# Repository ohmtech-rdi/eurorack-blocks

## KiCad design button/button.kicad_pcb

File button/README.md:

# button

## Description

This block is a simple trigger push button.
Its design is detailed [here](./documentation/design.md).

## Connecting

- This block needs its `GND` to be connected to the ground. All `GND` pins are connected
   internally.
- The signal `OUT` is the button signal. It should be connected to any GPIO of the
   target MCU, **preferably non-analog** GPIOs. See [Daisy Seed pinout](https://images.squarespace-cdn.com/content/v1/58d03fdc1b10e3bf442567b8/1591827747342-HCXMM2NNR26SP5F4U2CJ/ke17ZwdGBToddI8pDm48kN5PbQBGNYbW-5Hm1pf8hRF7gQa3H78H3Y0txjaiv_0fDoOvxcdMmMKkDsyUqMSsMWxHk725yiiHCCLfrh8O1z4YTzHvnKhyp6Da-NYroOW3ZGjoBKy3azqku80C789l0kLp48N9LluBiCpBrPZntaz462IffsVrAff3VJkwKncM1HZuDnV98dfxM9yHlqFkUQ/DaisyPinoutRev4%404x.png?format=500w) for details.

## Using

```c++
int main ()
{
   using namespace erb;
   
   Module module;
   Button button (module, Pin23);   // 1.
   
   module.run ([&](){
      if (button.pressed ()) ...    // 2.
      if (button.held ()) ...       // 3.
      if (button.released ()) ...   // 4.
   });
}
```

1. Attach the button to the module and specify the same pin as the one used for connecting,
2. The button was just pressed,
3. The button is held down,
4. The button was just released.

The `Button` class reference is available [here](./documentation/reference.md).

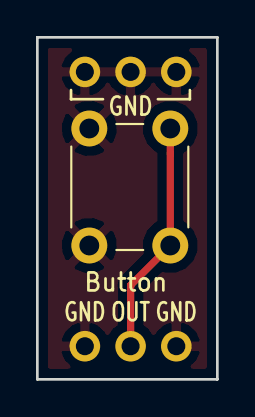
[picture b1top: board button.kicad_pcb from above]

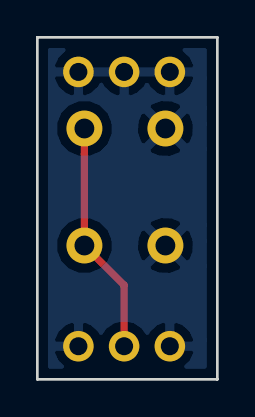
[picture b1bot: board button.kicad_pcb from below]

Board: 2 copper layers, 10.0 x 19.0 mm, 3 parts (2 on the bottom side), 2 nets.

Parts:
J1: POWER; PinHeader_1x03_P2.54mm_Vertical
J2: OUT; PinHeader_1x03_P2.54mm_Vertical
SW1: SW_Push_Dual; SW_PUSH_6mm_H7.3mm

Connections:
GND: J1.1, J1.2, J1.3, J2.1, J2.3, SW1.1
OUT: J2.2, SW1.2

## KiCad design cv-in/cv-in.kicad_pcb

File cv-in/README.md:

# cv-in

## Description

This block is a simple analog CV input.
Its design is detailed [here](./documentation/design.md).

## Connecting

- This block needs its `GND` to be connected to the ground. All `GND` pins are connected
   internally,
- This block needs its `-12V` to be connected to the `-12V` of the `power-bus`,
- This block needs its `3V3A` to be connected to the Daisy Seed 3V3 Analog Power I/O on Pin 21,
- The `NOP` pin can be either connected to:
   - `GND` to send (slightly noisy) zeros to the software implementation,
   - Cascading the `DI` signal from another `cv-in` block,
   - A pseudo-random predefined signal to detect a jack connection
      as explained on the Mutable Instruments forums
      [here](https://forum.mutable-instruments.net/t/plaits-normalization-probe/14358/2)
      and implemented
      [here](https://github.com/pichenettes/eurorack/blob/master/plaits/ui.cc#L368).
- The signal `OUT` is the CV input signal. It should be connected to any Analog GPIO of the
   target MCU. See [Daisy Seed pinout](https://images.squarespace-cdn.com/content/v1/58d03fdc1b10e3bf442567b8/1591827747342-HCXMM2NNR26SP5F4U2CJ/ke17ZwdGBToddI8pDm48kN5PbQBGNYbW-5Hm1pf8hRF7gQa3H78H3Y0txjaiv_0fDoOvxcdMmMKkDsyUqMSsMWxHk725yiiHCCLfrh8O1z4YTzHvnKhyp6Da-NYroOW3ZGjoBKy3azqku80C789l0kLp48N9LluBiCpBrPZntaz462IffsVrAff3VJkwKncM1HZuDnV98dfxM9yHlqFkUQ/DaisyPinoutRev4%404x.png?format=500w) for details.

The `DI` pin is the signal coming out directly from the jack connector and should be left floating
if not used.

The pseudo-random predefined signal jack detection method allows,
from a user experience point of view, to dissociate a non-connected
jack from a connected jack at `GND` level.

## Using

```c++
int main ()
{
   using namespace erb;
   
   Module module;
   CvIn cv_in (module, AdcPin6);    // 1.
   
   module.run ([&](){
      float cv_value = cv_in;       // 2.
   });
}
```

1. Attach the CV to the module and specify the same analog pin as the one used for connecting,
2. Retrieve the bipolar (in the `-1.f` to `1.f` range) floating-point CV value from the
   -8V to 8V electrical range.

The `CvIn` class reference is available [here](./documentation/reference.md).

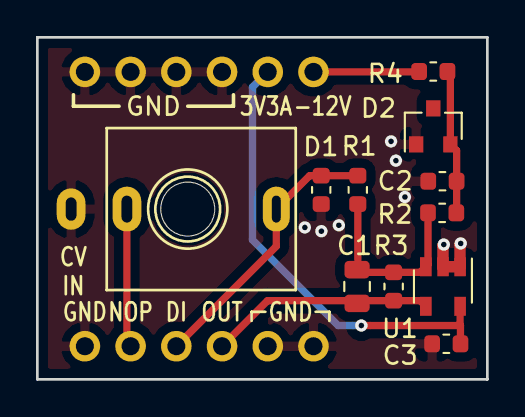
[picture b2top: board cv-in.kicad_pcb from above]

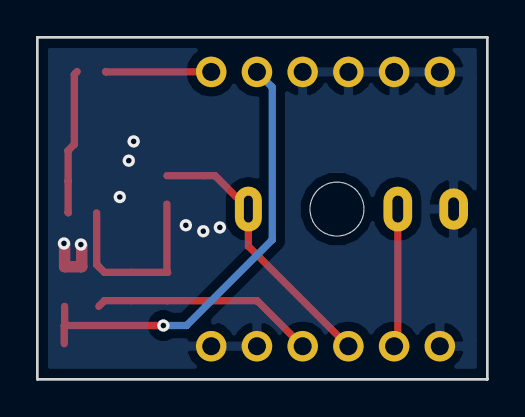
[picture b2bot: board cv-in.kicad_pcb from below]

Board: 2 copper layers, 25.0 x 19.0 mm, 13 parts (2 on the bottom side), 8 nets.

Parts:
C1: 33n; C_0805_2012Metric
C2: 1u; C_0603_1608Metric
C3: 100n; C_0603_1608Metric
D1: D_TVS; R_0603_1608Metric
D2: LM4040DBZ-10; SOT-23
J1: IN; ThonkiconnJack
J2: OUT; PinHeader_1x06_P2.54mm_Vertical
J3: POWER; PinHeader_1x06_P2.54mm_Vertical
R1: 100k; R_0603_1608Metric
R2: 120k; R_0603_1608Metric
R3: 20k; R_0603_1608Metric
R4: 4.99k; R_0603_1608Metric
U1: MCP6001U; SOT-23-5

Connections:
+3V3: C3.2, J3.5, U1.5
-12V: J3.6, R4.2
DI: D1.1, J1.T, J2.4, R1.2
GND: C2.1, C3.1, D1.2, D2.1, J1.S, J2.1, J2.2, J2.6, J3.1, J3.2, J3.3, J3.4, U1.1, U1.2
NOP: J1.TN, J2.5
unnamed: C1.2, R1.1, R2.1, R3.2, U1.3
OUT: C1.1, J2.3, R3.1, U1.4
VREF-10: C2.2, D2.2, R2.2, R4.1

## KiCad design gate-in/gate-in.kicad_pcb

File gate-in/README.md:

# gate-in

## Description

This block is a simple gate input.
Its design is detailed [here](./documentation/design.md).

## Connecting

- This block needs its `GND` to be connected to the ground. All `GND` pins are connected
   internally,
- This block needs its `3V3D` to be connected to the Daisy Seed 3V3 Digital Power I/O on Pin 38,
- The `NOP` pin can be either connected to:
   - `GND` to send zeros to the software implementation,
   - Cascading the `DI` signal from another `gate-in` block,
   - A pseudo-random predefined signal to detect a jack connection
      as explained on the Mutable Instruments forums
      [here](https://forum.mutable-instruments.net/t/plaits-normalization-probe/14358/2)
      and implemented
      [here](https://github.com/pichenettes/eurorack/blob/master/plaits/ui.cc#L368).
- The signal `OUT` is the Gate input signal. It should be connected to any Digital
   (and preferably non-Analog) GPIO
   of the target MCU. See [Daisy Seed pinout](https://images.squarespace-cdn.com/content/v1/58d03fdc1b10e3bf442567b8/1591827747342-HCXMM2NNR26SP5F4U2CJ/ke17ZwdGBToddI8pDm48kN5PbQBGNYbW-5Hm1pf8hRF7gQa3H78H3Y0txjaiv_0fDoOvxcdMmMKkDsyUqMSsMWxHk725yiiHCCLfrh8O1z4YTzHvnKhyp6Da-NYroOW3ZGjoBKy3azqku80C789l0kLp48N9LluBiCpBrPZntaz462IffsVrAff3VJkwKncM1HZuDnV98dfxM9yHlqFkUQ/DaisyPinoutRev4%404x.png?format=500w) for details.

The `DI` pin is the signal coming out directly from the jack connector and should be left floating
if not used.

The pseudo-random predefined signal jack detection method allows,
from a user experience point of view, to dissociate a non-connected
jack from a connected jack at `GND` level.

## Using

```c++
int main ()
{
   using namespace erb;
   
   Module module;
   GateIn gate_in (module, Pin7);   // 1.
   
   module.run ([&](){
      bool gate_value = gate_in;    // 2.
   });
}
```

1. Attach the gate to the module and specify the same digital pin as the one used for connecting,
2. Retrieve the boolean gate value.

The `GateIn` class reference is available [here](./documentation/reference.md).

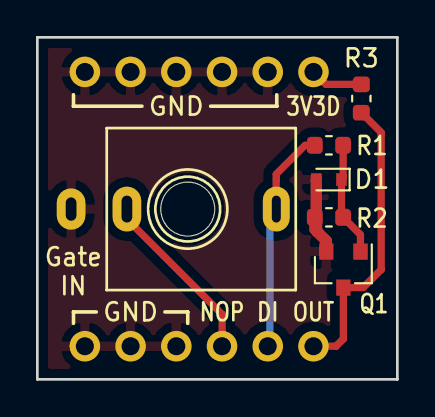
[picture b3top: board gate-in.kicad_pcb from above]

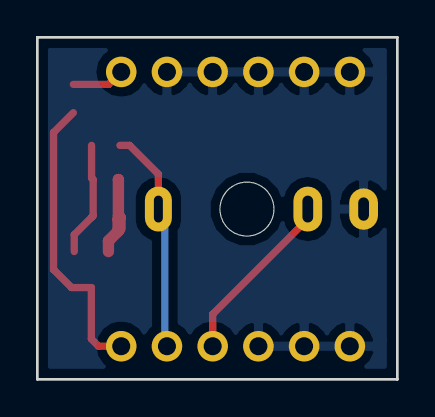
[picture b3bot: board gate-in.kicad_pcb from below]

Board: 2 copper layers, 20.0 x 19.0 mm, 8 parts (2 on the bottom side), 6 nets.

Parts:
D1: 1N4148; D_SOD-523
J1: IN; ThonkiconnJack
J2: OUT; PinHeader_1x06_P2.54mm_Vertical
J3: POWER; PinHeader_1x06_P2.54mm_Vertical
Q1: MMBT3904; SOT-23
R1, R2: 100k; R_0603_1608Metric
R3: 10k; R_0603_1608Metric

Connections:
+3V3: J3.6, R3.1
DI: J1.T, J2.2, R1.2
GND: D1.2, J1.S, J2.4, J2.5, J2.6, J3.1, J3.2, J3.3, J3.4, J3.5, Q1.2, R2.1
NOP: J1.TN, J2.3
unnamed: D1.1, Q1.1, R1.1, R2.2
OUT: J2.1, Q1.3, R3.2

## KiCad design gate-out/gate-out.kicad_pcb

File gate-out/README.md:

# gate-out

## Description

This block is a simple 3V3 gate output compatible with Eurorack levels.

It is adapted from the [Mutable Instruments Frames schematics](https://mutable-instruments.net/modules/frames/downloads/frames_v03.pdf).

## Usage

This block provides a standard eurorack jack connector that is used for eurorack gate output
+5V signals.

### Power

This module needs to be connected to the `+12V` and `GND` lines from the power block.

All `GND` pins are internally connected in the block.

### Signal

The signal `IN` is the gate triggering signal. It should be connected to any GPIO of the
target MCU, **preferably non-analog** GPIOs.

When using Daisy Seed as a development platform, see
[its pinout](https://images.squarespace-cdn.com/content/v1/58d03fdc1b10e3bf442567b8/1591827747342-HCXMM2NNR26SP5F4U2CJ/ke17ZwdGBToddI8pDm48kN5PbQBGNYbW-5Hm1pf8hRF7gQa3H78H3Y0txjaiv_0fDoOvxcdMmMKkDsyUqMSsMWxHk725yiiHCCLfrh8O1z4YTzHvnKhyp6Da-NYroOW3ZGjoBKy3azqku80C789l0kLp48N9LluBiCpBrPZntaz462IffsVrAff3VJkwKncM1HZuDnV98dfxM9yHlqFkUQ/DaisyPinoutRev4%404x.png?format=500w)
for details. The Daisy Seed has a total of 31 GPIOs, only 12 of which are analog.

## Design

> Gerber renders made with [tracespace view](https://tracespace.io/view/).

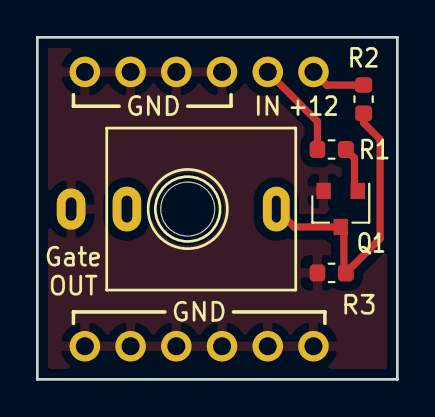
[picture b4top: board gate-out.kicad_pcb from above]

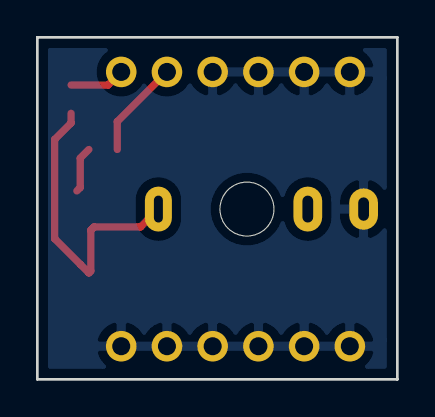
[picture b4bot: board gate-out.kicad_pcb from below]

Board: 2 copper layers, 20.0 x 19.0 mm, 7 parts (2 on the bottom side), 5 nets.

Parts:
J1: OUT; ThonkiconnJack
J2: GND; PinHeader_1x06_P2.54mm_Vertical
J3: IN; PinHeader_1x06_P2.54mm_Vertical
Q1: MMBT3904; SOT-23
R1: 10k; R_0603_1608Metric
R2: 4.7k; R_0603_1608Metric
R3: 3.3k; R_0603_1608Metric

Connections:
+12V: J3.1, R2.1
GND: J1.S, J2.1, J2.2, J2.3, J2.4, J2.5, J2.6, J3.3, J3.4, J3.5, J3.6, Q1.2, R3.2
IN: J3.2, R1.2
unnamed: J1.T, Q1.3, R2.2, R3.1
unnamed: Q1.1, R1.1

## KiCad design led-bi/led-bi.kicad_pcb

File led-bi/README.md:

# led-bi

## Description

This block is a simple dichromatic LED.
Its design is detailed [here](./documentation/design.md).

## Connecting

- This block needs its `GND` to be connected to the ground. All `GND` pins are connected
   internally.
- The signal `INR` is the LED red signal. It should be connected to any GPIO of the
   target MCU, **preferably non-analog** GPIOs. See [Daisy Seed pinout](https://images.squarespace-cdn.com/content/v1/58d03fdc1b10e3bf442567b8/1591827747342-HCXMM2NNR26SP5F4U2CJ/ke17ZwdGBToddI8pDm48kN5PbQBGNYbW-5Hm1pf8hRF7gQa3H78H3Y0txjaiv_0fDoOvxcdMmMKkDsyUqMSsMWxHk725yiiHCCLfrh8O1z4YTzHvnKhyp6Da-NYroOW3ZGjoBKy3azqku80C789l0kLp48N9LluBiCpBrPZntaz462IffsVrAff3VJkwKncM1HZuDnV98dfxM9yHlqFkUQ/DaisyPinoutRev4%404x.png?format=500w) for details.
- The signal `ING` is the LED green signal. It should be connected to any GPIO of the
   target MCU, **preferably non-analog** GPIOs. See [Daisy Seed pinout](https://images.squarespace-cdn.com/content/v1/58d03fdc1b10e3bf442567b8/1591827747342-HCXMM2NNR26SP5F4U2CJ/ke17ZwdGBToddI8pDm48kN5PbQBGNYbW-5Hm1pf8hRF7gQa3H78H3Y0txjaiv_0fDoOvxcdMmMKkDsyUqMSsMWxHk725yiiHCCLfrh8O1z4YTzHvnKhyp6Da-NYroOW3ZGjoBKy3azqku80C789l0kLp48N9LluBiCpBrPZntaz462IffsVrAff3VJkwKncM1HZuDnV98dfxM9yHlqFkUQ/DaisyPinoutRev4%404x.png?format=500w) for details.

## Using

```c++
int main ()
{
   using namespace erb;
   
   Module module;
   LedBi led (module, Pin23, Pin24);      // 1.
   
   module.run ([&](){
      led.on (LedBi::Color::Red);         // 2.
      led.off ();                         // 3.
      led.pulse (LedBi::Color::Yellow);   // 4.
      led.blink (LedBi::Color::Green);    // 5.
   });
}
```

1. Attach the LED to the module and specify the same pins as the one used for connecting,
2. The LED is turned on with a red color,
3. The LED is turned off,
4. The LED is shorlty pulsed with a yellow color,
5. The LED is blinking with a green color.

The `LedBi` class reference is available [here](./documentation/reference.md).

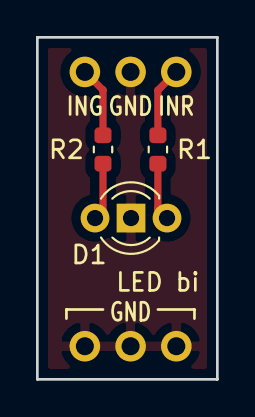
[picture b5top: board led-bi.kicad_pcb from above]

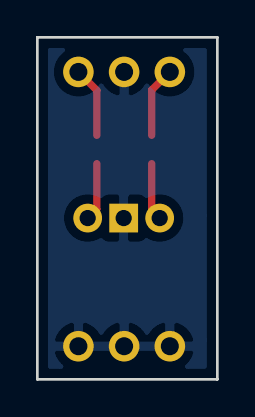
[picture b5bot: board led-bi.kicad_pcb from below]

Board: 2 copper layers, 10.0 x 19.0 mm, 5 parts (2 on the bottom side), 5 nets.

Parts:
D1: LED_Dual_ACA; LED_D3.0mm-3
J1: IN; PinHeader_1x03_P2.54mm_Vertical
J2: GND; PinHeader_1x03_P2.54mm_Vertical
R1, R2: 100; R_0603_1608Metric

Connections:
GND: D1.2, J1.2, J2.1, J2.2, J2.3
ING: J1.1, R2.2
INR: J1.3, R1.2
unnamed: D1.1, R1.1
unnamed: D1.3, R2.1

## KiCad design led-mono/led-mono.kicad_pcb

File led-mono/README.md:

# led-mono

## Description

This block is a simple monochromatic green LED.

It is adapted from the [Mutable Instuments Frames schematics](https://mutable-instruments.net/modules/frames/downloads/frames_v03.pdf).

## Usage

This block provides a simple LED.

### Power

This block needs to be connected to `GND`.

### Signal

The signal `IN` is the LED signal. It should be connected to any GPIO of the
target MCU, **preferably non-analog** GPIOs.

When using Daisy Seed as a development platform, see
[its pinout](https://images.squarespace-cdn.com/content/v1/58d03fdc1b10e3bf442567b8/1591827747342-HCXMM2NNR26SP5F4U2CJ/ke17ZwdGBToddI8pDm48kN5PbQBGNYbW-5Hm1pf8hRF7gQa3H78H3Y0txjaiv_0fDoOvxcdMmMKkDsyUqMSsMWxHk725yiiHCCLfrh8O1z4YTzHvnKhyp6Da-NYroOW3ZGjoBKy3azqku80C789l0kLp48N9LluBiCpBrPZntaz462IffsVrAff3VJkwKncM1HZuDnV98dfxM9yHlqFkUQ/DaisyPinoutRev4%404x.png?format=500w)
for details. The Daisy Seed has a total of 31 GPIOs, only 12 of which are analog.

## Design

> Gerber renders made with [tracespace view](https://tracespace.io/view/).

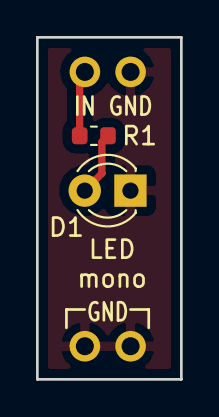
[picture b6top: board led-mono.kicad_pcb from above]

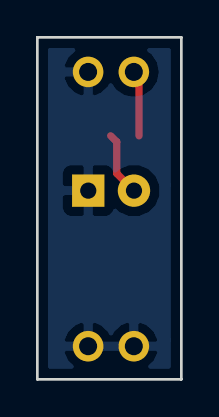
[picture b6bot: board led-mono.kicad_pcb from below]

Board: 2 copper layers, 8.0 x 19.0 mm, 4 parts (2 on the bottom side), 3 nets.

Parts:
D1: LED; LED_D3.0mm
J1: IN; PinHeader_1x02_P2.54mm_Vertical
J2: GND; PinHeader_1x02_P2.54mm_Vertical
R1: 100; R_0603_1608Metric

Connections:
GND: D1.1, J1.2, J2.1, J2.2
IN: J1.1, R1.2
unnamed: D1.2, R1.1
